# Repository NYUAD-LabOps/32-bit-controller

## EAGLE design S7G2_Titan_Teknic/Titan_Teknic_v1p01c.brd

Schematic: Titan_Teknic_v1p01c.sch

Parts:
AFID1, AFID2, AFID3, AFID4, AFID5, AFID6: FIDUCIAL_1MM
C1, C2: 24pF; 0402
C3: 100pF; 0402
C4, C7, C9, C10, C12, C13, C15, C19, C20, C22, C24, C25, C26, C27, C29, C30, C33, C34, C35, C36, C38, C39, C40, C42, C43: 0.1uF; 0402
C5, C6, C16, C23: 10uF; 0402
C8, C14: 22uF; 0402
C11: 2.2uF; 0402
C17, C18: 18pF; 0402
C21, C28, C41: 1uF; 0402
C31: 100uF_Tant; C1210
C32, C37: 12pF; 0402
FB1: FB2_603; 0603
J1: SD_CARD
J2: 4-pos; 1X4_3.81MM_PITCH
J3: 10-pos; 2X5
J4: 20-pos; 2_X_10_.1_INCH
J5, J10, J11, J12, J19, J20, J27, J28, J31, J32: CONN_530470310_PICOBLADE_X_3; CON_530470310_MOL
J6: USB-A; USB_A_SMT
J7: USB-B-Micro; USB_MICRO-B
J8, J39: 2_X_10_HEADER_GENERIC; 2_X_10_.1_INCH
J9, J15, J16, J23, J24: 2-pos; 2_3.81MM_PITCH
J13, J14, J17, J18, J21, J22, J25, J26, J29, J30, J33, J34: TEKNIC_MOTOR_8PIN; CON_39281083
L1: 2.2uH; 1008
LED1, LED3, LED4, LED5, LED6, LED7, LED8, LED9, LED10, LED11, LED12, LED13, LED14, LED15, LED16: Green; 0805
R1: 6K49; 0402
R2, R3, R13, R19, R20, R23, R24, R34, R53, R56, R59, R74, R77, R80, R83, R98, R101: 10K0; 0402
R4, R6: 1K5; 0402
R5, R7, R8, R31, R32, R33, R36, R51, R52, R55, R58, R73, R76, R79, R82, R97, R100: 470R0; 0402
R9, R10, R11, R12: 33R0; 0402
R14, R15: 1K0; 0402
R16: 15K0; 0402
R17, R18: 27R0; 0402
R21: 30K0; 0402
R22: 2K2; 0402
R25, R26, R27, R102, R103, R104, R105, R106, R107, R108: 100K; 0402
R28, R35, R54, R57, R60, R75, R78, R81, R84, R99: 2.2K; 0402
R29, R30, R49, R50: 500R0; 0402
R37, R41, R42, R43, R47, R48, R61, R65, R66, R67, R71, R72, R85, R89, R90, R91, R95, R96, R109, R113, R114, R115, R119, R120, R133, R137, R138, R139, R143, R144, R157, R161, R162, R163, R167, R168: 1k; 0805
R38, R39, R40, R44, R45, R46, R62, R63, R64, R68, R69, R70, R86, R87, R88, R92, R93, R94, R110, R111, R112, R116, R117, R118, R134, R135, R136, R140, R141, R142, R158, R159, R160, R164, R165, R166: 33; 0805
RJ1: RJ45; RJ45_TH_ELEC
U1: KSZ8081_QFN_24; QFN-24-M
U2: AP2151DWG-7; SOT-23-5
U3: S7G2LQFP176; LQFP176_24X24
U5, U6, U7, U8, U9, U10, U11, U12, U13, U14, U15, U16, U17, U18, U19, U20, U21, U22, U23, U24, U25, U26, U27, U28, U29, U30, U34, U35, U36, U37, U38, U39, U46, U47, U48, U49, U50, U51, U58, U59, U60, U61, U62, U63, U70, U71, U72, U73, U74, U75: NPN; SOT323
U$1, U$2, U$7, U$8: RELAY_KYOTO_KF0604D
X1: 25MHz; SMD_3225
X2: 24MHz; SMD_3225
X3: 32.768KHz; SMD_X_2_PADS

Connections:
A_A_DIR: R111.1, U3.73 (P9_5)
A_A_ENABLE: R112.1, U3.72 (P9_6)
A_A_HLFB_OUT: J25.5 (5-HLFB-)
A_A_MI_DIR: J25.7 (7-INPUT_A-), R113.1, U47.3 (C(3))
A_A_MI_ENABLE: J25.8 (8-ENABLE-), R114.1, U48.3 (C(3))
A_A_MI_STEP: J25.6 (6-INPUT_B-), R109.1, U46.3 (C(3))
A_A_STEP: R110.1, U3.74 (P3_12)
A_B_DIR: R117.1, U3.76 (P3_10)
A_B_ENABLE: R118.1, U3.75 (P3_11)
A_B_HLFB_OUT: J26.5 (5-HLFB-)
A_B_MI_DIR: J26.7 (7-INPUT_A-), R119.1, U50.3 (C(3))
A_B_MI_ENABLE: J26.8 (8-ENABLE-), R120.1, U51.3 (C(3))
A_B_MI_STEP: J26.6 (6-INPUT_B-), R115.1, U49.3 (C(3))
A_B_STEP: R116.1, U3.77 (P3_9)
B_MI_DIR: J34.7 (7-INPUT_A-), R167.1, U74.3 (C(3))
C58: C12.P$1 (1), RJ1.4 (CT1)
C60: C13.P$1 (1), RJ1.5 (CT2)
CRS_DV: R12.P$2 (2), U1.15 (CRS_DV/PHYAD[1:0])
C_A_DIR: R135.1, U3.58 (P9_0)
C_A_ENABLE: R136.1, U3.57 (P3_15)
C_A_HLFB_OUT: J29.5 (5-HLFB-)
C_A_MI_DIR: J29.7 (7-INPUT_A-), R137.1, U59.3 (C(3))
C_A_MI_ENABLE: J29.8 (8-ENABLE-), R138.1, U60.3 (C(3))
C_A_MI_STEP: J29.6 (6-INPUT_B-), R133.1, U58.3 (C(3))
C_A_STEP: R134.1, U3.59 (P9_1)
C_B_DIR: R141.1, U3.70 (P9_8)
C_B_ENABLE: R142.1, U3.68 (P2_1/MD)
C_B_HLFB_OUT: J30.5 (5-HLFB-)
C_B_MI_DIR: J30.7 (7-INPUT_A-), R143.1, U62.3 (C(3))
C_B_MI_ENABLE: J30.8 (8-ENABLE-), R144.1, U63.3 (C(3))
C_B_MI_STEP: J30.6 (6-INPUT_B-), R139.1, U61.3 (C(3))
C_B_STEP: R140.1, U3.71 (P9_7)
D+: J7.P$3 (D+), R18.P$2 (2)
D-: J7.P$2 (D-), R17.P$2 (2)
ESTOP: R79.P$2 (2), R80.P$2 (2), U3.69 (P2_0(INPUT_ONLY)), U21.2 (E(1))
ESTOP_RET: J20.1, R78.P$1 (1)
ETH: U1.16 (REF_CLK), U3.9 (P7_1)
ETH_CRS_DV: R12.P$1 (1), U3.13 (P7_5)
ETH_IRQ14: R2.P$1 (1), U1.18 (INTRP), U3.159 (P0_10/AN103)
ETH_MDC: R4.P$1 (1), U1.11 (MDC), U3.4 (P4_3)
ETH_MDIO: R6.P$1 (1), U1.10 (MDIO), U3.5 (P4_4)
ETH_RESET: C6.P$1 (1), R3.P$1 (1), U1.24 (!RST), U3.172 (P8_6)
ETH_RXD0: R10.P$1 (1), U3.10 (P7_2)
ETH_RXD1: R9.P$1 (1), U3.11 (P7_3)
ETH_RX_ER: R11.P$1 (1), U3.12 (P7_4)
ETH_TXD0: U1.20 (TXD0), U3.8 (P7_0)
ETH_TXD1: U1.21 (TXD1), U3.7 (P4_6)
ETH_TXD_EN: U1.19 (TXEN), U3.6 (P4_5)
GND: C1.P$2 (2), C2.P$2 (2), C3.P$2 (2), C4.P$2 (2), C5.P$2 (2), C6.P$2 (2), C7.P$2 (2), C8.P$2 (2), C9.P$2 (2), C10.P$2 (2), C11.P$2 (2), C12.P$2 (2), C13.P$2 (2), C14.P$2 (2), C15.P$2 (2), C16.P$2 (2), C17.P$2 (2), C18.P$2 (2), C19.P$1 (1), C20.P$1 (1), C21.P$1 (1), C22.P$1 (1), C23.P$2 (2), C24.P$1 (1), C25.P$1 (1), C26.P$2 (2), C27.P$1 (1), C28.P$2 (2), C29.P$2 (2), C30.P$1 (1), C31.2, C32.P$2 (2), C33.P$2 (2), C34.P$1 (1), C35.P$1 (1), C36.P$2 (2), C37.P$2 (2), C38.P$1 (1), C39.P$2 (2), C40.P$2 (2), C41.P$2 (2), C42.P$2 (2), C43.P$1 (1), J1.6 (SUPPLY_VOLTAGE_GROUND), J2.P$1, J3.6, J3.8, J3.10, J5.2, J6.GND, J7.P$5 (GND), J10.2, J11.2, J12.2, J19.2, J20.2, J27.2, J28.2, J31.2, J32.2, J39.P$1, J39.P$3, J39.P$5, J39.P$7, J39.P$9, J39.P$11, J39.P$13, J39.P$15, J39.P$17, J39.P$19, LED1.2 (C), LED3.2 (C), LED6.2 (C), LED7.2 (C), LED10.2 (C), LED11.2 (C), LED12.2 (C), LED13.2 (C), LED14.2 (C), LED15.2 (C), LED16.2 (C), R1.P$1 (1), R21.P$1 (1), R22.P$1 (1), R23.P$1 (1), R24.P$1 (1), R34.P$1 (1), R53.P$1 (1), R56.P$1 (1), R59.P$1 (1), R74.P$1 (1), R77.P$1 (1), R80.P$1 (1), R83.P$1 (1), R98.P$1 (1), R101.P$1 (1), RJ1.8, RJ1.10 (GLO), U1.22 (GND), U1.25, U2.2 (GND), U3.22 (VSS1), U3.28 (AVSS_USBHS), U3.29 (PVSS_USBHS), U3.30 (VSS2_USBHS), U3.33 (VSS1_USBHS), U3.35 (VSSIO), U3.45 (VSS_USB), U3.60 (VSS(IO)2), U3.63 (VSS(IO/DCDC)), U3.66 (VCC_DCDC(IO/DCDC)), U3.83 (VSS(IO)3), U3.98 (VSS(IO)4), U3.111 (VSS(IO)5), U3.124 (VSS(IO)6), U3.139 (VSS(IO)7), U3.150 (VSS(IO)8), U3.153 (VREFL), U3.156 (AVSS0), U3.157 (VREFL0), U3.170 (VSS(IO)9), U6.2 (E(1)), U7.2 (E(1)), U10.2 (E(1)), U11.2 (E(1)), U12.2 (E(1)), U13.2 (E(1)), U14.2 (E(1)), U15.2 (E(1)), U16.2 (E(1)), U17.2 (E(1)), U22.2 (E(1)), U23.2 (E(1)), U24.2 (E(1)), U25.2 (E(1)), U26.2 (E(1)), U27.2 (E(1)), U34.2 (E(1)), U35.2 (E(1)), U36.2 (E(1)), U37.2 (E(1)), U38.2 (E(1)), U39.2 (E(1)), U46.2 (E(1)), U47.2 (E(1)), U48.2 (E(1)), U49.2 (E(1)), U50.2 (E(1)), U51.2 (E(1)), U58.2 (E(1)), U59.2 (E(1)), U60.2 (E(1)), U61.2 (E(1)), U62.2 (E(1)), U63.2 (E(1)), U70.2 (E(1)), U71.2 (E(1)), U72.2 (E(1)), U73.2 (E(1)), U74.2 (E(1)), U75.2 (E(1)), X1.2, X1.4, X2.2, X2.4
GNDE: J1.S1 (SHIELD), J1.S2 (SHIELD), J1.S3 (SHIELD), J1.S4 (SHIELD), J2.P$4, J6.SHLD1 (SHIELD_1), J6.SHLD2 (SHIELD_2), J7.P$6 (SHIELD1), J7.P$7 (SHIELD2), J7.P$8 (SHIELD3), J7.P$9 (SHIELD4), RJ1.13 (GNDE0), RJ1.14 (GNDE1)
ID: J7.P$4 (ID)
IIC_1_SCL: J8.P$8, R14.P$2 (2), U3.132 (P1_0)
IIC_1_SDA: J8.P$7, R15.P$2 (2), U3.131 (P1_1)
LED1/SPEED: RJ1.11 (YLO), U1.23 (LED0/ANEN_SPEED)
LS_01: R33.P$2 (2), R34.P$2 (2), U3.50 (P2_6), U5.2 (E(1))
LS_01_RET: J32.1, R28.P$1 (1)
LS_02: R36.P$2 (2), R53.P$2 (2), U3.51 (P2_5), U8.2 (E(1))
LS_02_RET: J31.1, R35.P$1 (1)
LS_03: R55.P$2 (2), R56.P$2 (2), U3.53 (P2_3), U9.2 (E(1))
LS_03_RET: J28.1, R54.P$1 (1)
LS_04: R73.P$2 (2), R74.P$2 (2), U3.54 (P2_2), U19.2 (E(1))
LS_04_RET: J27.1, R60.P$1 (1)
LS_05: R58.P$2 (2), R59.P$2 (2), U3.81 (P3_5), U18.2 (E(1))
LS_05_RET: J19.1, R57.P$1 (1)
LS_06: R76.P$2 (2), R77.P$2 (2), U3.82 (P3_4), U20.2 (E(1))
LS_06_RET: J12.1, R75.P$1 (1)
LS_07: R97.P$2 (2), R98.P$2 (2), U3.86 (P3_2), U29.2 (E(1))
LS_07_RET: J11.1, R84.P$1 (1)
LS_08: R82.P$2 (2), R83.P$2 (2), U3.87 (P3_1), U28.2 (E(1))
LS_08_RET: J5.1, R81.P$1 (1)
LS_09: R100.P$2 (2), R101.P$2 (2), U3.92 (P1_11), U30.2 (E(1))
LS_09_RET: J10.1, R99.P$1 (1)
unnamed: C24.P$2 (2), U3.148 (VCL2)
unnamed: LED1.1 (A), R5.P$1 (1)
unnamed: C33.P$1 (1), U3.19 (VCLO)
unnamed: C42.P$1 (1), U3.62 (VCL1)
unnamed: R23.P$2 (2), U3.64 (VLO1(DCDC))
unnamed: R24.P$2 (2), U3.65 (VLO2(DCDC))
unnamed: R22.P$2 (2), U3.27 (USBHS_RREF)
unnamed: R28.P$2 (2), U5.1 (B(2))
unnamed: LED3.1 (A), R33.P$1 (1)
unnamed: R35.P$2 (2), U8.1 (B(2))
unnamed: LED6.1 (A), R36.P$1 (1)
unnamed: R39.2, U11.1 (B(2))
unnamed: R40.2, U12.1 (B(2))
unnamed: R38.2, U10.1 (B(2))
unnamed: R45.2, U14.1 (B(2))
unnamed: R46.2, U15.1 (B(2))
unnamed: R44.2, U13.1 (B(2))
unnamed: R29.P$2 (2), U6.1 (B(2))
unnamed: LED4.2 (C), U6.3 (C(3)), U$1.P$1 (VC-)
unnamed: R30.P$2 (2), U7.1 (B(2))
unnamed: LED5.2 (C), U7.3 (C(3)), U$2.P$1 (VC-)
unnamed: LED5.1 (A), R31.P$1 (1)
unnamed: LED4.1 (A), R32.P$1 (1)
unnamed: R63.2, U23.1 (B(2))
unnamed: R64.2, U24.1 (B(2))
unnamed: R62.2, U22.1 (B(2))
unnamed: R69.2, U26.1 (B(2))
unnamed: R70.2, U27.1 (B(2))
unnamed: R68.2, U25.1 (B(2))
unnamed: R54.P$2 (2), U9.1 (B(2))
unnamed: LED7.1 (A), R55.P$1 (1)
unnamed: R57.P$2 (2), U18.1 (B(2))
unnamed: LED10.1 (A), R58.P$1 (1)
unnamed: R60.P$2 (2), U19.1 (B(2))
unnamed: LED11.1 (A), R73.P$1 (1)
unnamed: R87.2, U35.1 (B(2))
unnamed: R88.2, U36.1 (B(2))
unnamed: R86.2, U34.1 (B(2))
unnamed: R93.2, U38.1 (B(2))
unnamed: R94.2, U39.1 (B(2))
unnamed: R92.2, U37.1 (B(2))
unnamed: R49.P$2 (2), U16.1 (B(2))
unnamed: LED8.2 (C), U16.3 (C(3)), U$7.P$1 (VC-)
unnamed: R50.P$2 (2), U17.1 (B(2))
unnamed: LED9.2 (C), U17.3 (C(3)), U$8.P$1 (VC-)
unnamed: LED9.1 (A), R51.P$1 (1)
unnamed: LED8.1 (A), R52.P$1 (1)
unnamed: R111.2, U47.1 (B(2))
unnamed: R112.2, U48.1 (B(2))
unnamed: R110.2, U46.1 (B(2))
unnamed: R117.2, U50.1 (B(2))
unnamed: R118.2, U51.1 (B(2))
unnamed: R116.2, U49.1 (B(2))
unnamed: R75.P$2 (2), U20.1 (B(2))
unnamed: LED12.1 (A), R76.P$1 (1)
unnamed: R78.P$2 (2), U21.1 (B(2))
unnamed: LED13.1 (A), R79.P$1 (1)
unnamed: R81.P$2 (2), U28.1 (B(2))
unnamed: LED14.1 (A), R82.P$1 (1)
unnamed: R135.2, U59.1 (B(2))
unnamed: R136.2, U60.1 (B(2))
unnamed: R134.2, U58.1 (B(2))
unnamed: R141.2, U62.1 (B(2))
unnamed: R142.2, U63.1 (B(2))
unnamed: R140.2, U61.1 (B(2))
unnamed: R84.P$2 (2), U29.1 (B(2))
unnamed: LED15.1 (A), R97.P$1 (1)
unnamed: R99.P$2 (2), U30.1 (B(2))
unnamed: LED16.1 (A), R100.P$1 (1)
unnamed: R159.2, U71.1 (B(2))
unnamed: R160.2, U72.1 (B(2))
unnamed: R158.2, U70.1 (B(2))
unnamed: R165.2, U74.1 (B(2))
unnamed: R166.2, U75.1 (B(2))
unnamed: R164.2, U73.1 (B(2))
NC: J8.P$6, RJ1.7, U3.79 (P3_7), U3.80 (P3_6), U3.85 (P3_3)
P0_00: J4.P$2, U3.169 (P0_0/AN0\00)
P0_01: J4.P$1, U3.168 (P0_1/AN001)
P0_02: J39.P$20, R25.P$1 (1), U3.167 (P0_2/AN002)
P0_03: J39.P$18, R26.P$1 (1), U3.166 (P0_3/PGAVSS000)
P0_04: J39.P$16, R27.P$1 (1), U3.165 (P0_4/AN100)
P0_05: J39.P$14, R102.P$1 (1), U3.164 (P0_5/AN101)
P0_06: J39.P$12, R103.P$1 (1), U3.163 (P0_6/AN102)
P0_07: J39.P$10, R104.P$1 (1), U3.162 (P0_7/PGVSS100)
P0_08: J39.P$8, R105.P$1 (1), U3.161 (P0_8/AN003)
P0_09: J39.P$6, R106.P$1 (1), U3.160 (P0_9/AN004)
P0_14: J39.P$4, R107.P$1 (1), U3.152 (P0_14/DA0/AN005/AN105)
P0_15: J39.P$2, R108.P$1 (1), U3.151 (P0_15/DA1/AN006/AN106)
P1_02: J8.P$10, U3.130 (P1_2)
P1_03: J8.P$9, U3.129 (P1_3)
P1_04: J8.P$11, U3.128 (P1_4)
P1_05: J8.P$13, U3.127 (P1_5)
P1_06: J8.P$15, U3.126 (P1_6)
P1_07: J8.P$17, U3.125 (P1_7)
P4_00: J4.P$7, U3.1 (P4_0)
P4_01: J4.P$8, U3.2 (P4_1)
P4_02: J4.P$9, U3.3 (P4_2)
P4_08: J4.P$20, U3.43 (P4_8)
P4_09: J4.P$19, U3.42 (P4_9)
P4_10: J4.P$18, U3.41 (P4_10)
P4_11: J4.P$17, U3.40 (P4_11)
P4_12: J4.P$16, U3.39 (P4_12)
P4_13: J4.P$15, U3.38 (P4_13)
P4_14: J4.P$14, U3.37 (P4_14)
P4_15: J4.P$13, U3.36 (P4_15)
P5_11: J4.P$6, U3.176 (P5_11)
P5_12: J4.P$5, U3.175 (P5_12)
P5_13: J4.P$4, U3.174 (P5_13)
P6_00: J8.P$19, U3.122 (P6_0)
P7_06: J4.P$10, U3.14 (P7_6)
P7_07: J4.P$11, U3.15 (P7_7)
P8_00: J8.P$5, U3.133 (P8_0)
P8_01: J8.P$3, U3.134 (P8_1)
P8_02: J8.P$4, U3.135 (P8_2)
P8_03: J8.P$1, U3.136 (P8_3)
P8_04: J8.P$2, U3.137 (P8_4)
P8_05: J4.P$3, U3.173 (P8_5)
PB_00: J4.P$12, U3.16 (PB_0)
R51: R7.P$1 (1), RJ1.12 (YHI)
R52: R8.P$1 (1), RJ1.9 (GHI)
RELAY_1: R29.P$1 (1), U3.56 (P3_14)
RELAY_2: R30.P$1 (1), U3.55 (P3_13)
RELAY_3: R49.P$1 (1), U3.52 (P2_4)
RELAY_4: R50.P$1 (1), U3.49 (P2_7)
RESET: C16.P$1 (1), J3.9, R13.P$1 (1), U3.67 (RES#)
REXT: C3.P$1 (1), R1.P$2 (2), U1.9 (REXT)
RO_NEG_1: J15.P$2, U$1.P$3 (VO-)
RO_NEG_2: J16.P$2, U$2.P$3 (VO-)
RO_NEG_3: J23.P$2, U$7.P$3 (VO-)
RO_NEG_4: J24.P$2, U$8.P$3 (VO-)
RO_POS_1: J15.P$1, U$1.P$4 (VO+)
RO_POS_2: J16.P$1, U$2.P$4 (VO+)
RO_POS_3: J23.P$1, U$7.P$4 (VO+)
RO_POS_4: J24.P$1, U$8.P$4 (VO+)
RXD0: R10.P$2 (2), U1.13 (RXD0)
RXD1: R9.P$2 (2), U1.12 (RXD1)
RXER: R11.P$2 (2), U1.17 (RXER)
RXM: RJ1.6 (RD-), U1.3 (RXM)
RXP: RJ1.3 (RD+), U1.4 (RXP)
SD1_CD: J1.10 (CD_SWITCH2), U3.146 (P5_6/AN019)
SD1_CLK: J1.5 (CLOCK), U3.140 (P5_0/AN016)
SD1_CMD: J1.3 (COMMAND/RESPONSE), U3.141 (P5_1/AN116)
SD1_DAT0: J1.7 (DATA_LINE[BIT_0]), U3.142 (P5_2/AN017)
SD1_DAT1: J1.8 (DATA_LINE[BIT_1]), U3.143 (P5_3/AN117)
SD1_DAT2: J1.1 (DATA_LINE[BIT_2]), U3.144 (P5_4/AN018)
SD1_DAT3: J1.2 (CARD_DETECT/DATA_LINE[BIT_3]), U3.145 (P5_5/AN118)
SD1_WP: J1.9 (CD_SWITCH1), U3.147 (P5_7/AN119)
TCK: J3.7, U3.88 (P3_0)
TDI: J3.1, U3.91 (P1_10)
TDO: J3.3, U3.90 (P1_9)
TMS: J3.5, U3.89 (P1_8)
TXM: RJ1.2 (TD-), U1.5 (TXM)
TXP: RJ1.1 (TD+), U1.6 (TXP)
USBHS_FAULT: R19.P$1 (1), U2.3 (FLG), U3.78 (P3_8)
USBHS_N: J6.D-, U3.31 (USBHS_DM)
USBHS_P: J6.D+, U3.32 (USBHS_DP)
USBHS_VBUS: C29.P$1 (1), C31.1, J6.VBUS, U2.5 (OUT), U3.17 (PB_1)
USBHS_VBUSEN: R20.P$1 (1), U2.1 (EN)
USB_N: R17.P$1 (1), U3.46 (USB_DM)
USB_P: R18.P$1 (1), U3.47 (USB_DP)
USB_VBUS_B: R16.P$1 (1), U3.44 (P4_7)
VBUS: C28.P$1 (1), J7.P$1 (VBUS), R16.P$2 (2), R21.P$2 (2)
VCL_F(FLASH): C34.P$2 (2), U3.112 (VCL_F(FLASH))
VDD: C4.P$1 (1), C5.P$1 (1), C7.P$1 (1), C14.P$1 (1), C15.P$1 (1), C19.P$2 (2), C20.P$2 (2), C21.P$2 (2), C22.P$2 (2), C25.P$2 (2), C27.P$2 (2), C30.P$2 (2), C35.P$2 (2), C36.P$1 (1), C38.P$2 (2), C39.P$1 (1), C40.P$1 (1), C41.P$1 (1), C43.P$2 (2), FB1.1, J1.4 (SUPPLY_VOLTAGE), J3.2, J3.4, L1.2, R2.P$2 (2), R3.P$2 (2), R4.P$2 (2), R5.P$2 (2), R6.P$2 (2), R7.P$2 (2), R8.P$2 (2), R13.P$2 (2), R14.P$1 (1), R15.P$1 (1), R25.P$2 (2), R26.P$2 (2), R27.P$2 (2), R102.P$2 (2), R103.P$2 (2), R104.P$2 (2), R105.P$2 (2), R106.P$2 (2), R107.P$2 (2), R108.P$2 (2), U1.14 (VDDIO), U3.25 (VCC1), U3.26 (AVCC_SUBHS), U3.34 (VCC_USBHS), U3.48 (VCC_USB), U3.61 (VCC(IO)2), U3.84 (VCC(IO)3), U3.97 (VCC(IO)4), U3.110 (VCC(IO)5), U3.123 (VCC(IO)6), U3.138 (VCC(IO)7), U3.149 (VCC(IO)8), U3.154 (VREFH), U3.155 (AVCC0), U3.158 (VREFH0), U3.171 (VCC(IO)9), U5.3 (C(3)), U8.3 (C(3)), U9.3 (C(3)), U18.3 (C(3)), U19.3 (C(3)), U20.3 (C(3)), U21.3 (C(3)), U28.3 (C(3)), U29.3 (C(3)), U30.3 (C(3))
VDD5: C23.P$1 (1), C26.P$1 (1), J2.P$3, R19.P$2 (2), R20.P$2 (2), R31.P$2 (2), R32.P$2 (2), R51.P$2 (2), R52.P$2 (2), U2.4 (VIN), U$1.P$2 (VC+), U$2.P$2 (VC+), U$7.P$2 (VC+), U$8.P$2 (VC+)
VDD12: J5.3, J9.P$1, J9.P$2, J10.3, J11.3, J12.3, J13.1 (1-HLFB+), J13.2 (2-INPUT_B+), J13.3 (3-INPUT_A+), J13.4 (4-ENABLE+), J14.1 (1-HLFB+), J14.2 (2-INPUT_B+), J14.3 (3-INPUT_A+), J14.4 (4-ENABLE+), J17.1 (1-HLFB+), J17.2 (2-INPUT_B+), J17.3 (3-INPUT_A+), J17.4 (4-ENABLE+), J18.1 (1-HLFB+), J18.2 (2-INPUT_B+), J18.3 (3-INPUT_A+), J18.4 (4-ENABLE+), J19.3, J20.3, J21.1 (1-HLFB+), J21.2 (2-INPUT_B+), J21.3 (3-INPUT_A+), J21.4 (4-ENABLE+), J22.1 (1-HLFB+), J22.2 (2-INPUT_B+), J22.3 (3-INPUT_A+), J22.4 (4-ENABLE+), J25.1 (1-HLFB+), J25.2 (2-INPUT_B+), J25.3 (3-INPUT_A+), J25.4 (4-ENABLE+), J26.1 (1-HLFB+), J26.2 (2-INPUT_B+), J26.3 (3-INPUT_A+), J26.4 (4-ENABLE+), J27.3, J28.3, J29.1 (1-HLFB+), J29.2 (2-INPUT_B+), J29.3 (3-INPUT_A+), J29.4 (4-ENABLE+), J30.1 (1-HLFB+), J30.2 (2-INPUT_B+), J30.3 (3-INPUT_A+), J30.4 (4-ENABLE+), J31.3, J32.3, J33.1 (1-HLFB+), J33.2 (2-INPUT_B+), J33.3 (3-INPUT_A+), J33.4 (4-ENABLE+), J34.1 (1-HLFB+), J34.2 (2-INPUT_B+), J34.3 (3-INPUT_A+), J34.4 (4-ENABLE+), R37.2, R41.2, R42.2, R43.2, R47.2, R48.2, R61.2, R65.2, R66.2, R67.2, R71.2, R72.2, R85.2, R89.2, R90.2, R91.2, R95.2, R96.2, R109.2, R113.2, R114.2, R115.2, R119.2, R120.2, R133.2, R137.2, R138.2, R139.2, R143.2, R144.2, R157.2, R161.2, R162.2, R163.2, R167.2, R168.2
VDDIN: J2.P$2, L1.1
VDD_1.2: C10.P$1 (1), C11.P$1 (1), U1.1 (VDD_1.2)
VDD_ENET1: C8.P$1 (1), C9.P$1 (1), FB1.2, U1.2 (VDDA_3.3)
WF_A_DIR: R159.1, U3.99 (P6_8)
WF_A_ENABLE: R160.1, U3.96 (P1_15)
WF_A_HLFB_OUT: J33.5 (5-HLFB-)
WF_A_MI_DIR: J33.7 (7-INPUT_A-), R161.1, U71.3 (C(3))
WF_A_MI_ENABLE: J33.8 (8-ENABLE-), R162.1, U72.3 (C(3))
WF_A_MI_STEP: J33.6 (6-INPUT_B-), R157.1, U70.3 (C(3))
WF_A_STEP: R158.1, U3.100 (P6_9)
WF_B_DIR: R165.1, U3.94 (P1_13)
WF_B_ENABLE: R166.1, U3.93 (P1_12)
WF_B_HLFB_OUT: J34.5 (5-HLFB-)
WF_B_MI_ENABLE: J34.8 (8-ENABLE-), R168.1, U75.3 (C(3))
WF_B_MI_STEP: J34.6 (6-INPUT_B-), R163.1, U73.3 (C(3))
WF_B_STEP: R164.1, U3.95 (P1_14)
XCIN: C32.P$1 (1), U3.20 (XCIN), X3.P$1
XCOUT: C37.P$1 (1), U3.21 (XCOUT), X3.P$2
XII: C1.P$1 (1), U1.8 (XI), X1.1
XOO: C2.P$1 (1), U1.7 (XO), X1.3
XTAL1: C17.P$1 (1), U3.23 (P2_13/XTAL), X2.1
XTAL2: C18.P$1 (1), U3.24 (P2_12/EXTAL), X2.3
X_A_DIR: R39.1, U3.117 (P6_5)
X_A_ENABLE: R40.1, U3.116 (P6_6)
X_A_HLFB_OUT: J13.5 (5-HLFB-)
X_A_MI_DIR: J13.7 (7-INPUT_A-), R41.1, U11.3 (C(3))
X_A_MI_ENABLE: J13.8 (8-ENABLE-), R42.1, U12.3 (C(3))
X_A_MI_STEP: J13.6 (6-INPUT_B-), R37.1, U10.3 (C(3))
X_A_STEP: R38.1, U3.118 (P6_4)
X_B_DIR: R45.1, U3.120 (P6_2)
X_B_ENABLE: R46.1, U3.119 (P6_3)
X_B_HLFB_OUT: J14.5 (5-HLFB-)
X_B_MI_DIR: J14.7 (7-INPUT_A-), R47.1, U14.3 (C(3))
X_B_MI_ENABLE: J14.8 (8-ENABLE-), R48.1, U15.3 (C(3))
X_B_MI_STEP: J14.6 (6-INPUT_B-), R43.1, U13.3 (C(3))
X_B_STEP: R44.1, U3.121 (P6_1)
Y_A_DIR: R63.1, U3.114 (PA_0)
Y_A_ENABLE: R64.1, U3.113 (PA_1)
Y_A_HLFB_OUT: J17.5 (5-HLFB-)
Y_A_MI_DIR: J17.7 (7-INPUT_A-), R65.1, U23.3 (C(3))
Y_A_MI_ENABLE: J17.8 (8-ENABLE-), R66.1, U24.3 (C(3))
Y_A_MI_STEP: J17.6 (6-INPUT_B-), R61.1, U22.3 (C(3))
Y_A_STEP: R62.1, U3.115 (P6_7)
Y_B_DIR: R69.1, U3.108 (PA_9)
Y_B_ENABLE: R70.1, U3.107 (PA_8)
Y_B_HLFB_OUT: J18.5 (5-HLFB-)
Y_B_MI_DIR: J18.7 (7-INPUT_A-), R71.1, U26.3 (C(3))
Y_B_MI_ENABLE: J18.8 (8-ENABLE-), R72.1, U27.3 (C(3))
Y_B_MI_STEP: J18.6 (6-INPUT_B-), R67.1, U25.3 (C(3))
Y_B_STEP: R68.1, U3.109 (PA_10)
Z_A_DIR: R87.1, U3.105 (P6_14)
Z_A_ENABLE: R88.1, U3.104 (P6_13)
Z_A_HLFB_OUT: J21.5 (5-HLFB-)
Z_A_MI_DIR: J21.7 (7-INPUT_A-), R89.1, U35.3 (C(3))
Z_A_MI_ENABLE: J21.8 (8-ENABLE-), R90.1, U36.3 (C(3))
Z_A_MI_STEP: J21.6 (6-INPUT_B-), R85.1, U34.3 (C(3))
Z_A_STEP: R86.1, U3.106 (P6_15)
Z_B_DIR: R93.1, U3.102 (P6_11)
Z_B_ENABLE: R94.1, U3.101 (P6_10)
Z_B_HLFB_OUT: J22.5 (5-HLFB-)
Z_B_MI_DIR: J22.7 (7-INPUT_A-), R95.1, U38.3 (C(3))
Z_B_MI_ENABLE: J22.8 (8-ENABLE-), R96.1, U39.3 (C(3))
Z_B_MI_STEP: J22.6 (6-INPUT_B-), R91.1, U37.3 (C(3))
Z_B_STEP: R92.1, U3.103 (P6_12)

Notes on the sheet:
Power Input
JTAG

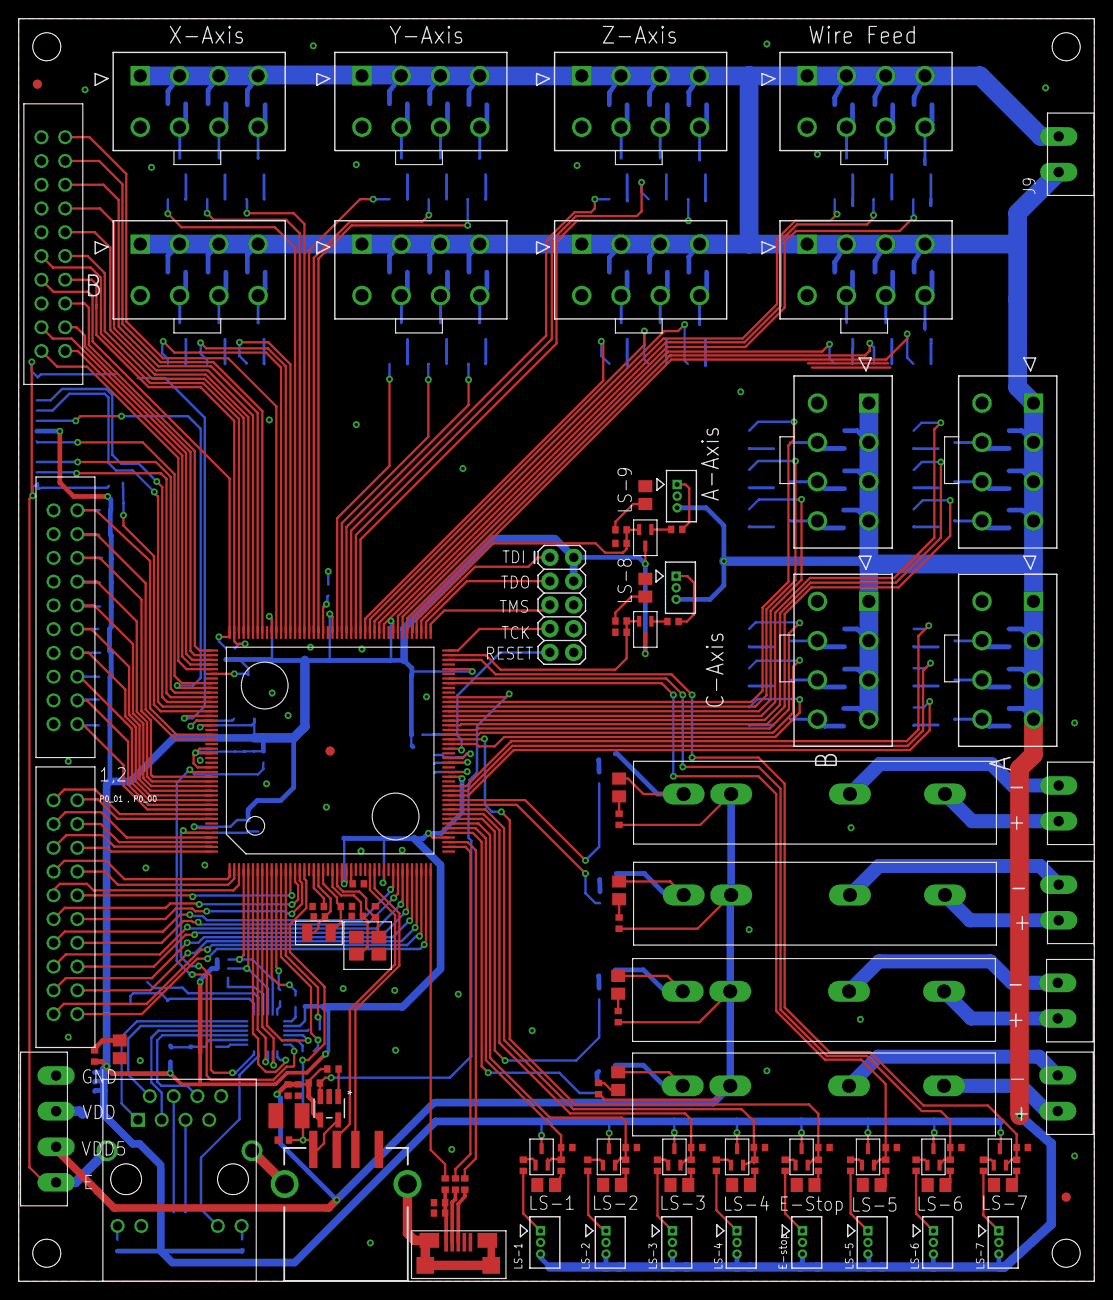
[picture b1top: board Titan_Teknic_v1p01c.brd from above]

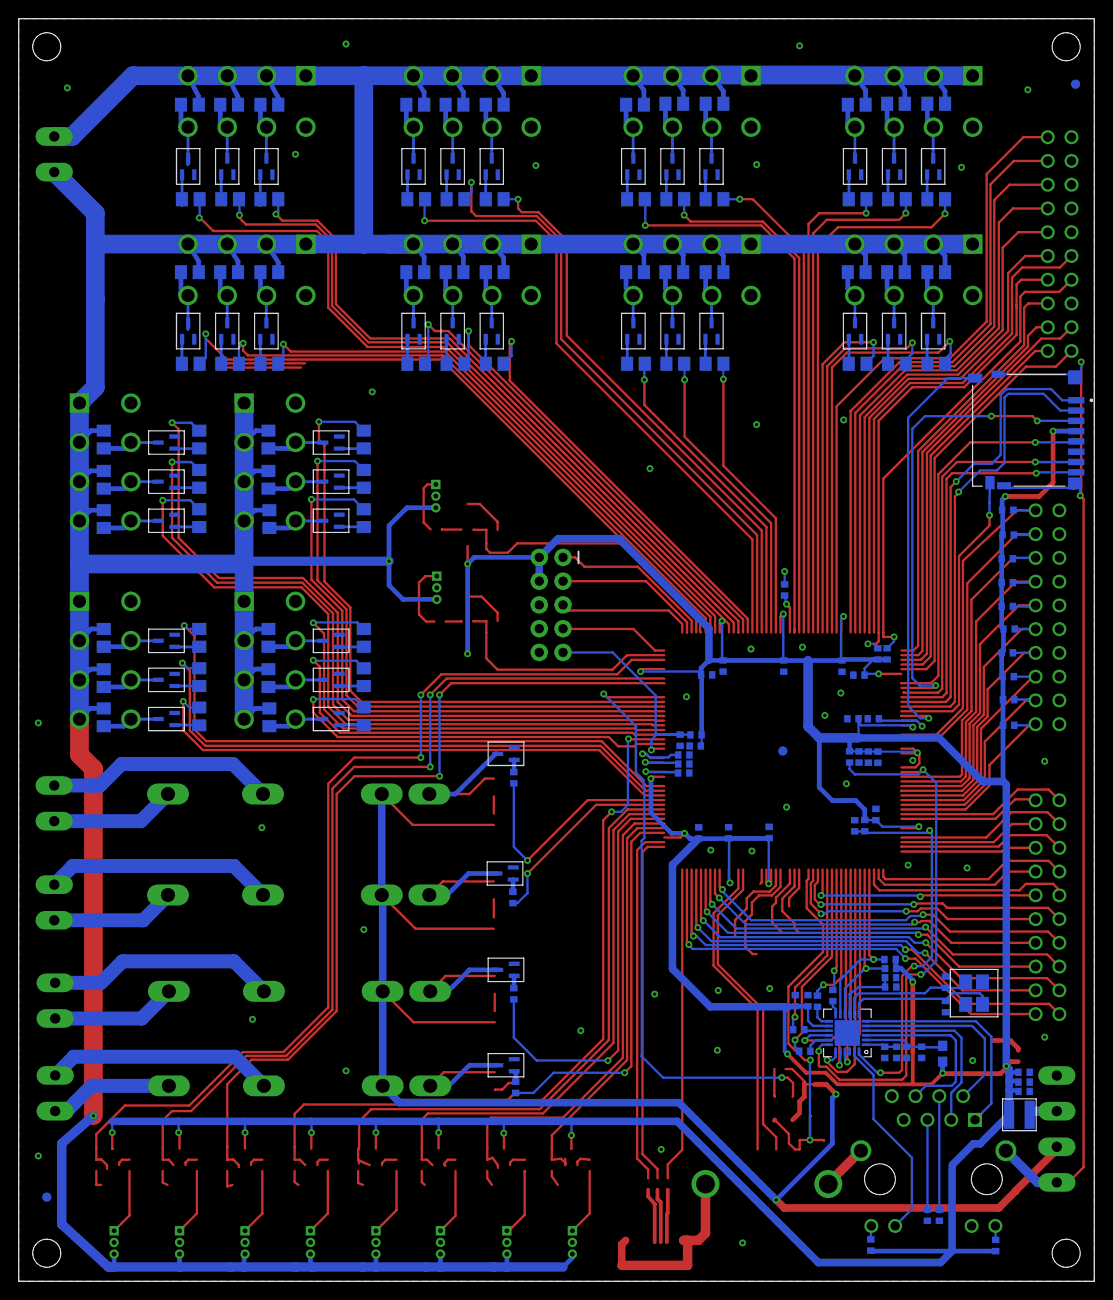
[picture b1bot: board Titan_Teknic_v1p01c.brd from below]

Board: 2 copper layers, 115.0 x 135.0 mm, 306 parts (183 on the bottom side), 289 nets.

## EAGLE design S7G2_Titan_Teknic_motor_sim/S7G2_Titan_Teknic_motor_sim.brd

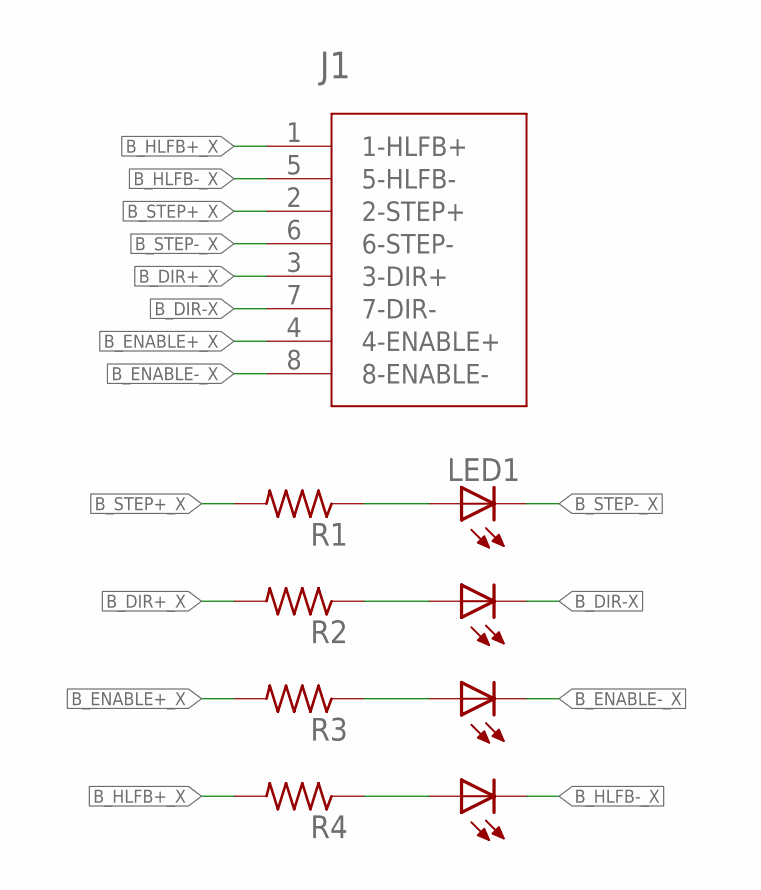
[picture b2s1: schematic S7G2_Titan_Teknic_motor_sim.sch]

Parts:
J1: TEKNIC_MOTOR_SD_8PIN; CON_39281083
LED1, LED2, LED3, LED4: Green; 0805
R1, R2, R3, R4: R_0805; 0805

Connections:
B_DIR+_X: J1.3 (3-DIR+), R2.2
B_DIR-X: J1.7 (7-DIR-), LED2.2 (C)
B_ENABLE+_X: J1.4 (4-ENABLE+), R3.2
B_ENABLE-_X: J1.8 (8-ENABLE-), LED3.2 (C)
B_HLFB+_X: J1.1 (1-HLFB+), R4.2
B_HLFB-_X: J1.5 (5-HLFB-), LED4.2 (C)
B_STEP+_X: J1.2 (2-STEP+), R1.2
B_STEP-_X: J1.6 (6-STEP-), LED1.2 (C)
unnamed: LED1.1 (A), R1.1
unnamed: LED2.1 (A), R2.1
unnamed: LED3.1 (A), R3.1
unnamed: LED4.1 (A), R4.1

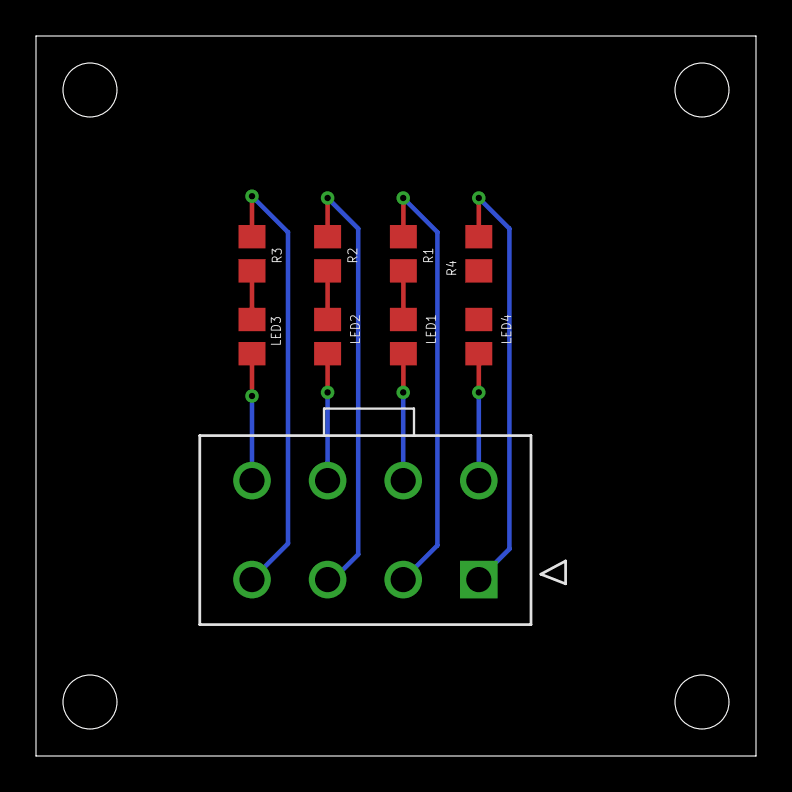
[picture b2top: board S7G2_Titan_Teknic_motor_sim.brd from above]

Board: 2 copper layers, 40.0 x 40.0 mm, 9 parts (0 on the bottom side), 12 nets.

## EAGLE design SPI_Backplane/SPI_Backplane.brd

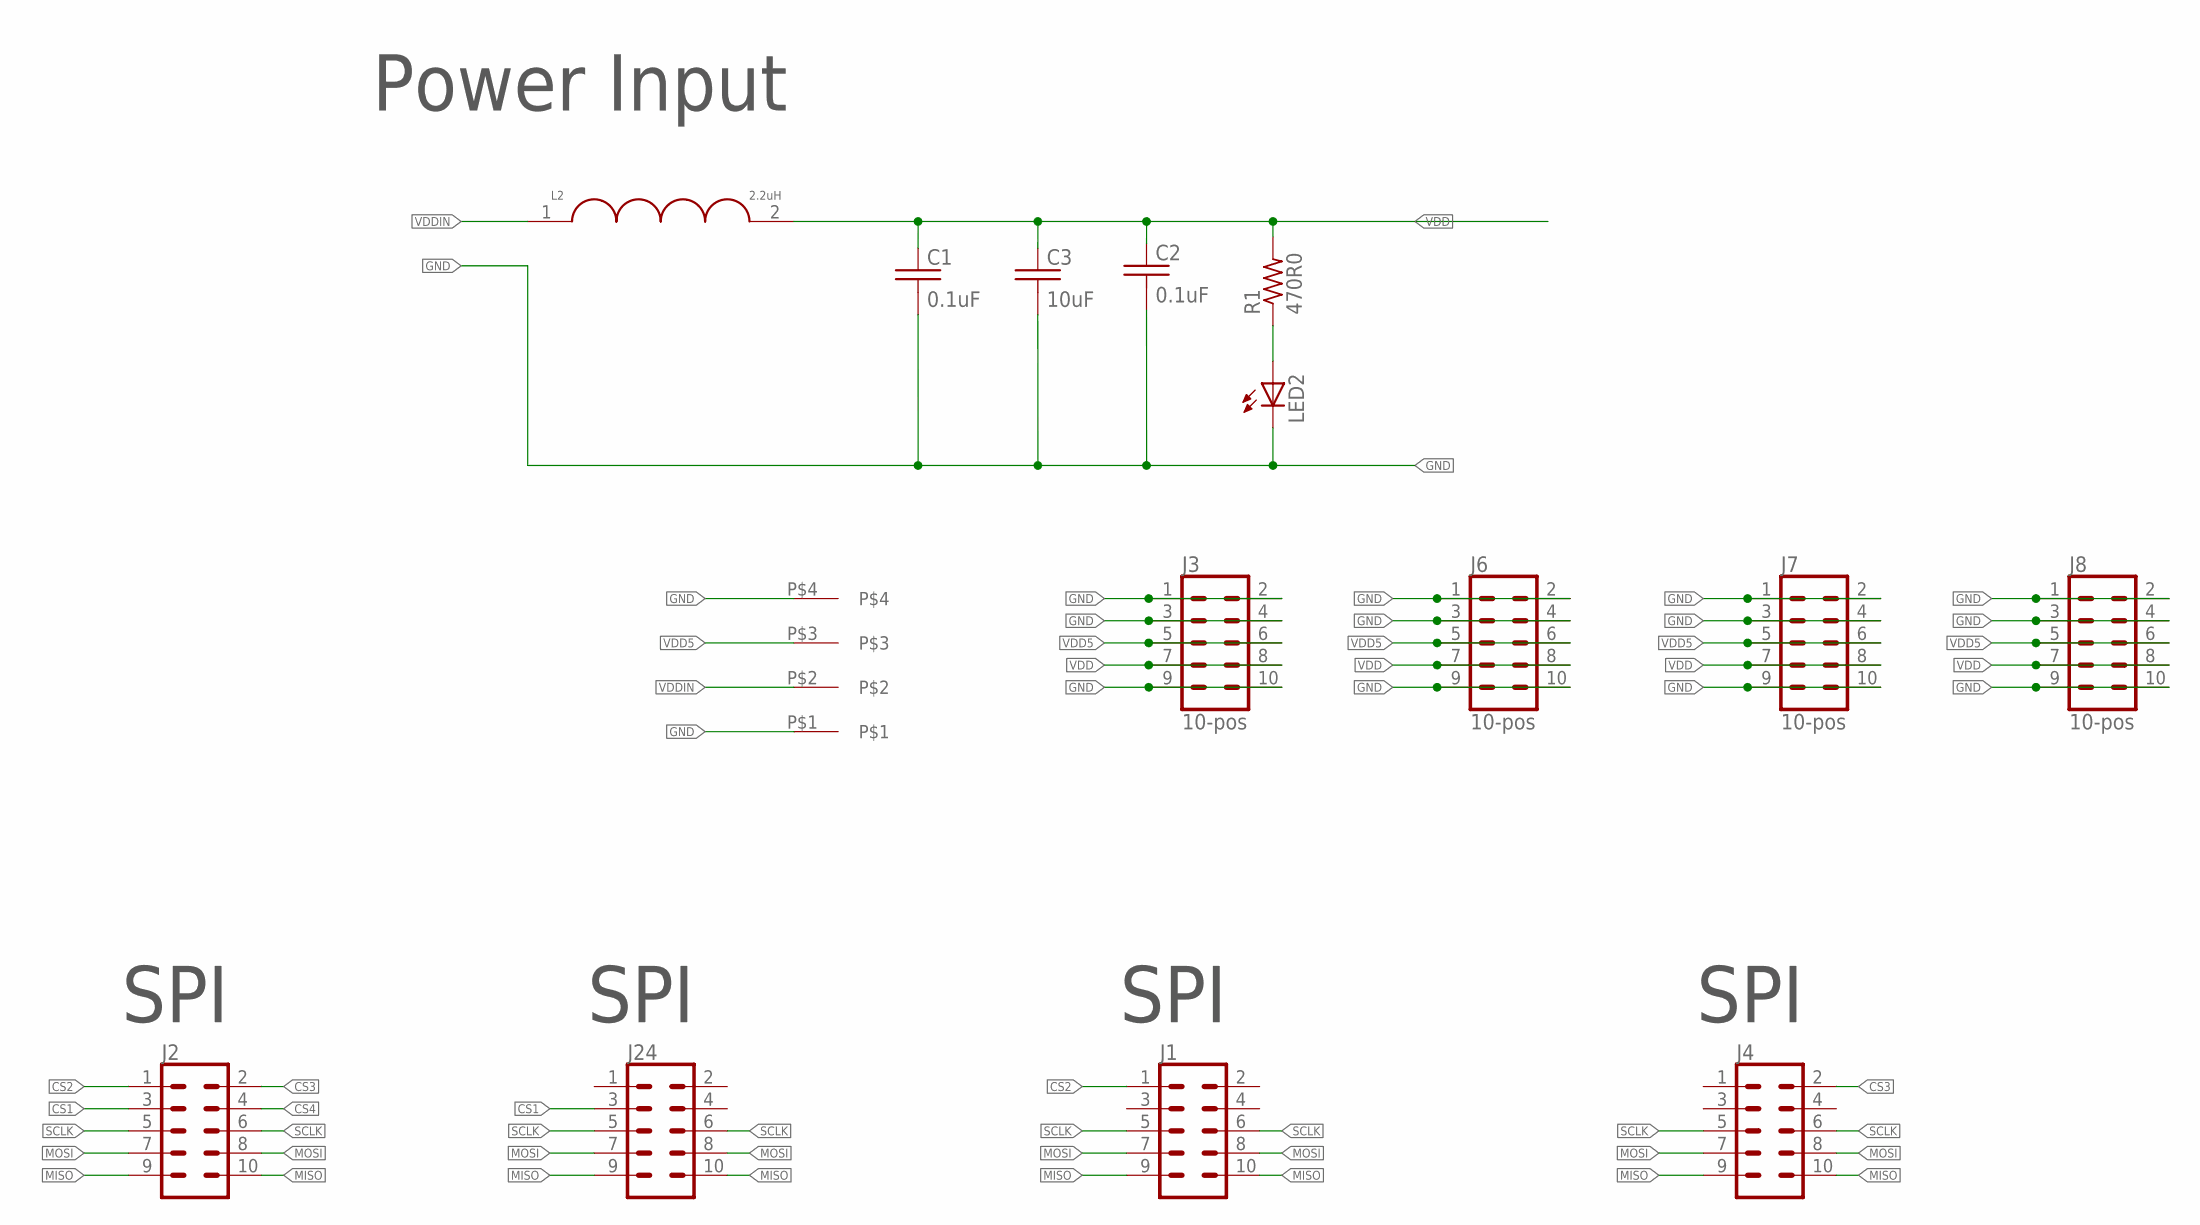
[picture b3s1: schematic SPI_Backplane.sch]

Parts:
C1, C2: 0.1uF; 0402
C3: 10uF; 0402
J1, J2, J4, J24: CONN_05X2PTH; 2X5
J3, J6, J7, J8: 10-pos; 2X5
J5: 4-pos; 1X4_3.81MM_PITCH
L2: 2.2uH; 1008
LED2: Green; 0805
R1: 470R0; 0402

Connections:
CS1: J2.3, J24.3
CS2: J1.1, J2.1
CS3: J2.2, J4.2
CS4: J2.4
GND: C1.P$2 (2), C2.P$2 (2), C3.P$2 (2), J3.1, J3.2, J3.3, J3.4, J3.9, J3.10, J5.P$1, J5.P$4, J6.1, J6.2, J6.3, J6.4, J6.9, J6.10, J7.1, J7.2, J7.3, J7.4, J7.9, J7.10, J8.1, J8.2, J8.3, J8.4, J8.9, J8.10, LED2.2 (C)
MISO: J1.9, J1.10, J2.9, J2.10, J4.9, J4.10, J24.9, J24.10
MOSI: J1.7, J1.8, J2.7, J2.8, J4.7, J4.8, J24.7, J24.8
unnamed: LED2.1 (A), R1.P$1 (1)
SCLK: J1.5, J1.6, J2.5, J2.6, J4.5, J4.6, J24.5, J24.6
VDD: C1.P$1 (1), C2.P$1 (1), C3.P$1 (1), J3.7, J3.8, J6.7, J6.8, J7.7, J7.8, J8.7, J8.8, L2.2, R1.P$2 (2)
VDD5: J3.5, J3.6, J5.P$3, J6.5, J6.6, J7.5, J7.6, J8.5, J8.6
VDDIN: J5.P$2, L2.1

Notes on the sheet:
Power Input
SPI

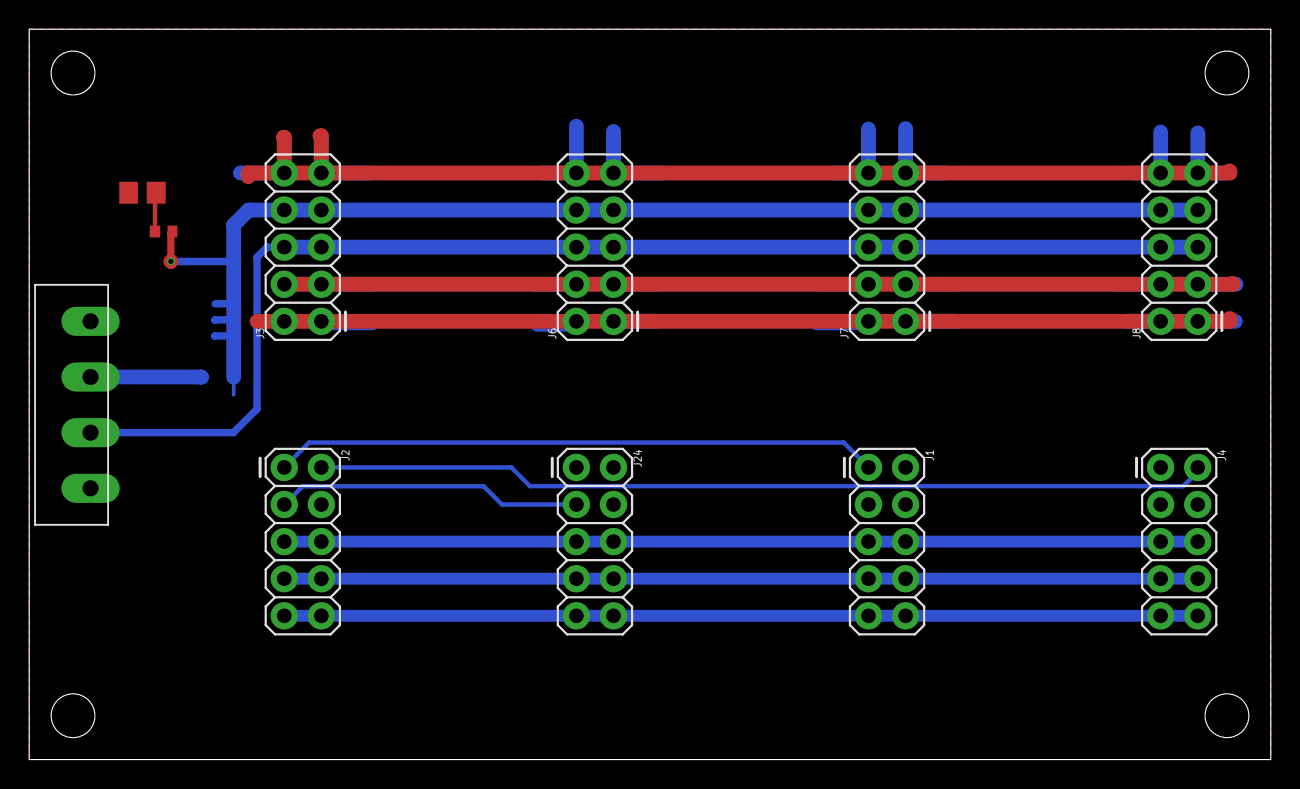
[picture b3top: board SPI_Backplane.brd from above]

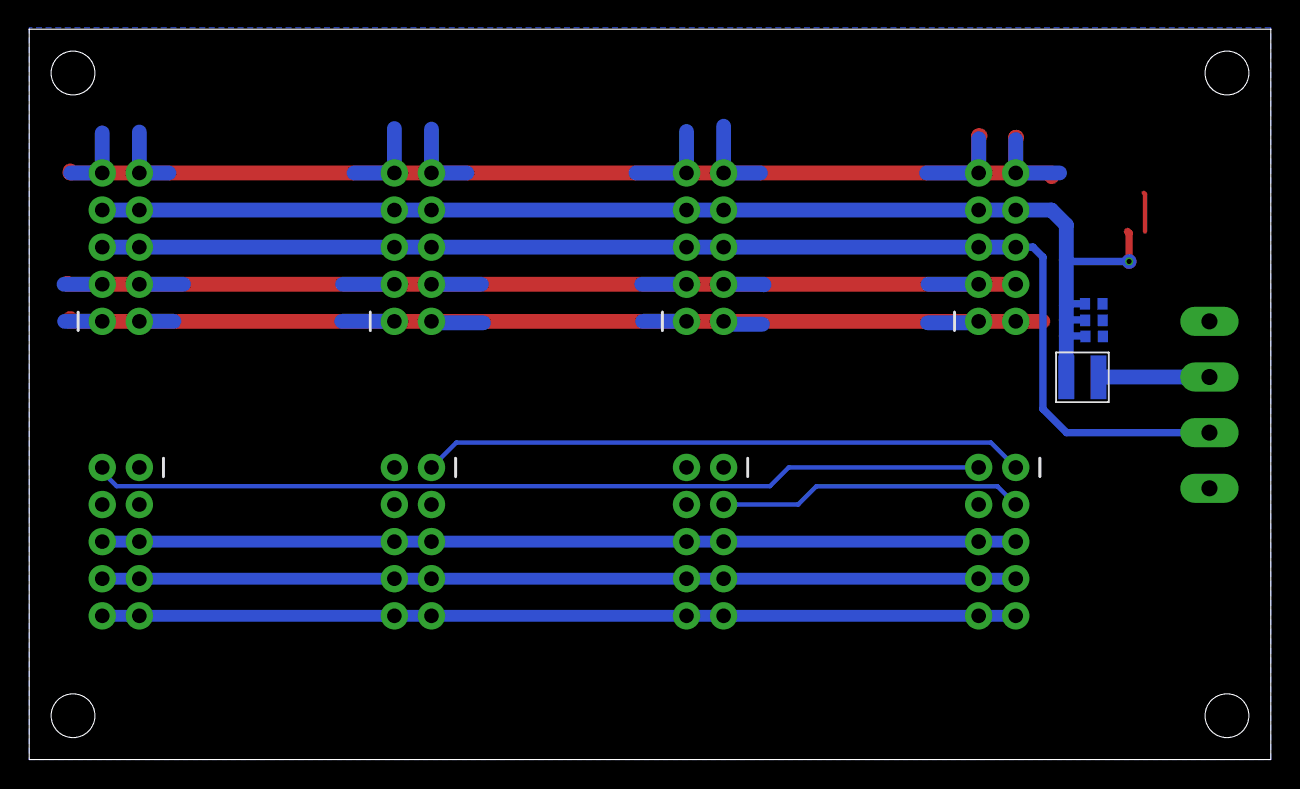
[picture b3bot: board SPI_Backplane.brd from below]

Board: 2 copper layers, 85.0 x 50.0 mm, 15 parts (4 on the bottom side), 11 nets.

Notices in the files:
parts and their libraries:
COPYRIGHT: Copyright (C) 2022 Ultra Librarian. All rights reserved.
COPYRIGHT: Copyright (C) 2023 Ultra Librarian. All rights reserved.
